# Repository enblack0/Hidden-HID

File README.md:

# Hidden-HID
Hidden HID is tiny USB device that can be concealed entirely inside a USB A port. 
Once inserted it is almost invisible to those unaware of its presence. 

It consists of a single 8x12x0.4mm PCB with USB contacts on the top layer and an STM32 on the bottom.
The additional height required to maintain contact with the USB pins is achieved with 3 1206 LEDs with height 1.8mm soldered to the pads on either side. These are not electrically connected.

Here you will find kicad design files. The firmware is a work in progress and not currently uploaded.

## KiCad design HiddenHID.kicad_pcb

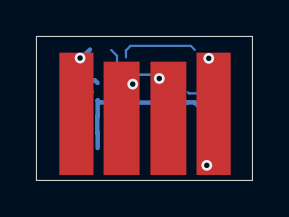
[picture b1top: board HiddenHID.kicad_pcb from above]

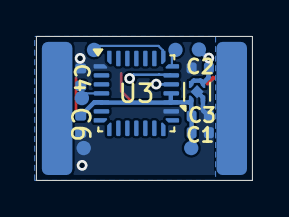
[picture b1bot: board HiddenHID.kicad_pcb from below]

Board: 2 copper layers, 12.0 x 8.0 mm, 14 parts (13 on the bottom side), 8 nets.

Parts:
C1: 4.7µ; C_0402_1005Metric_noSS
C2, C3, C6: 1µ; C_0402_1005Metric_noSS
C4: 100n; C_0402_1005Metric_noSS
J1: USB_A; usb-PCB
TP1, TP2, TP3, TP4, TP5, TP6: TestPoint_Pad_D0.8mm
U2: NCP115AMX330TCG; OnSemi_XDFN4-1EP_1.0x1.0mm_EP0.52x0.52mm
U3: STM32F042G6Ux; QFN-28_4x4mm_P0.5mm

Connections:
+3.3V: C1.2, C3.2, C6.1, TP2.1, U2.1 (OUT), U3.5 (VDDA), U3.17 (VDD), U3.18 (VDDIO2)
+5V: C2.1, J1.1 (VBUS), TP1.1, U2.3 (EN), U2.4 (IN)
/DM: J1.2 (D-), U3.19 (PA9/PA11)
/DP: J1.3 (D+), U3.20 (PA10/PA12)
/SWCLK: TP5.1, U3.22 (PA14)
/SWDIO: TP4.1, U3.21 (PA13)
/nRST: C4.1, TP6.1, U3.4 (NRST)
GND: C1.1, C2.2, C3.1, C4.2, C6.2, J1.4 (GND), TP3.1, U2.2 (GND), U2.5 (GND), U3.1 (PB8), U3.16 (VSSA)
